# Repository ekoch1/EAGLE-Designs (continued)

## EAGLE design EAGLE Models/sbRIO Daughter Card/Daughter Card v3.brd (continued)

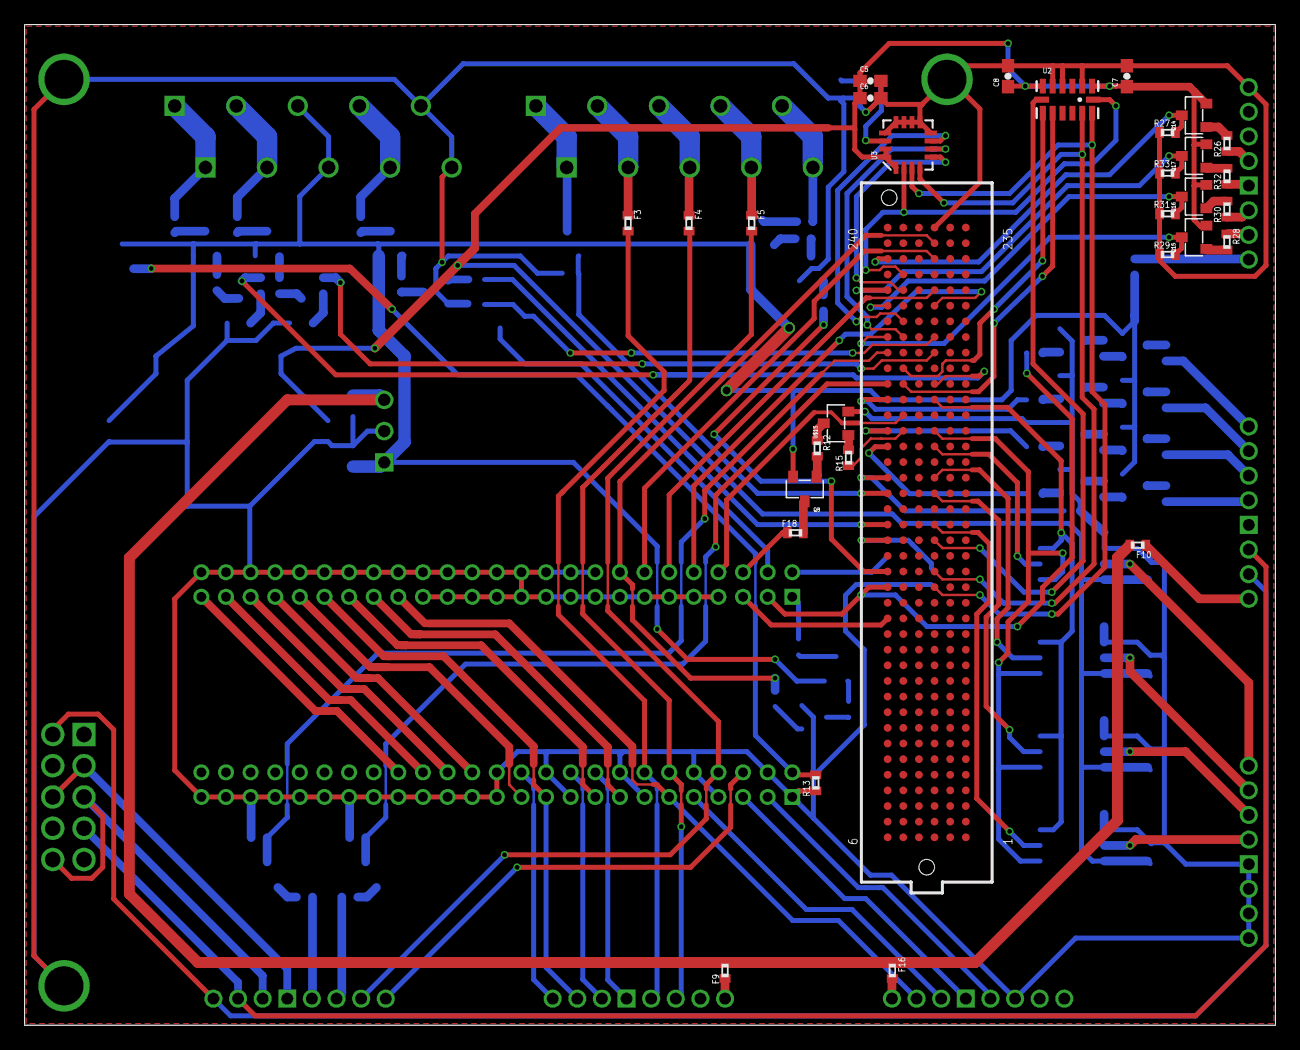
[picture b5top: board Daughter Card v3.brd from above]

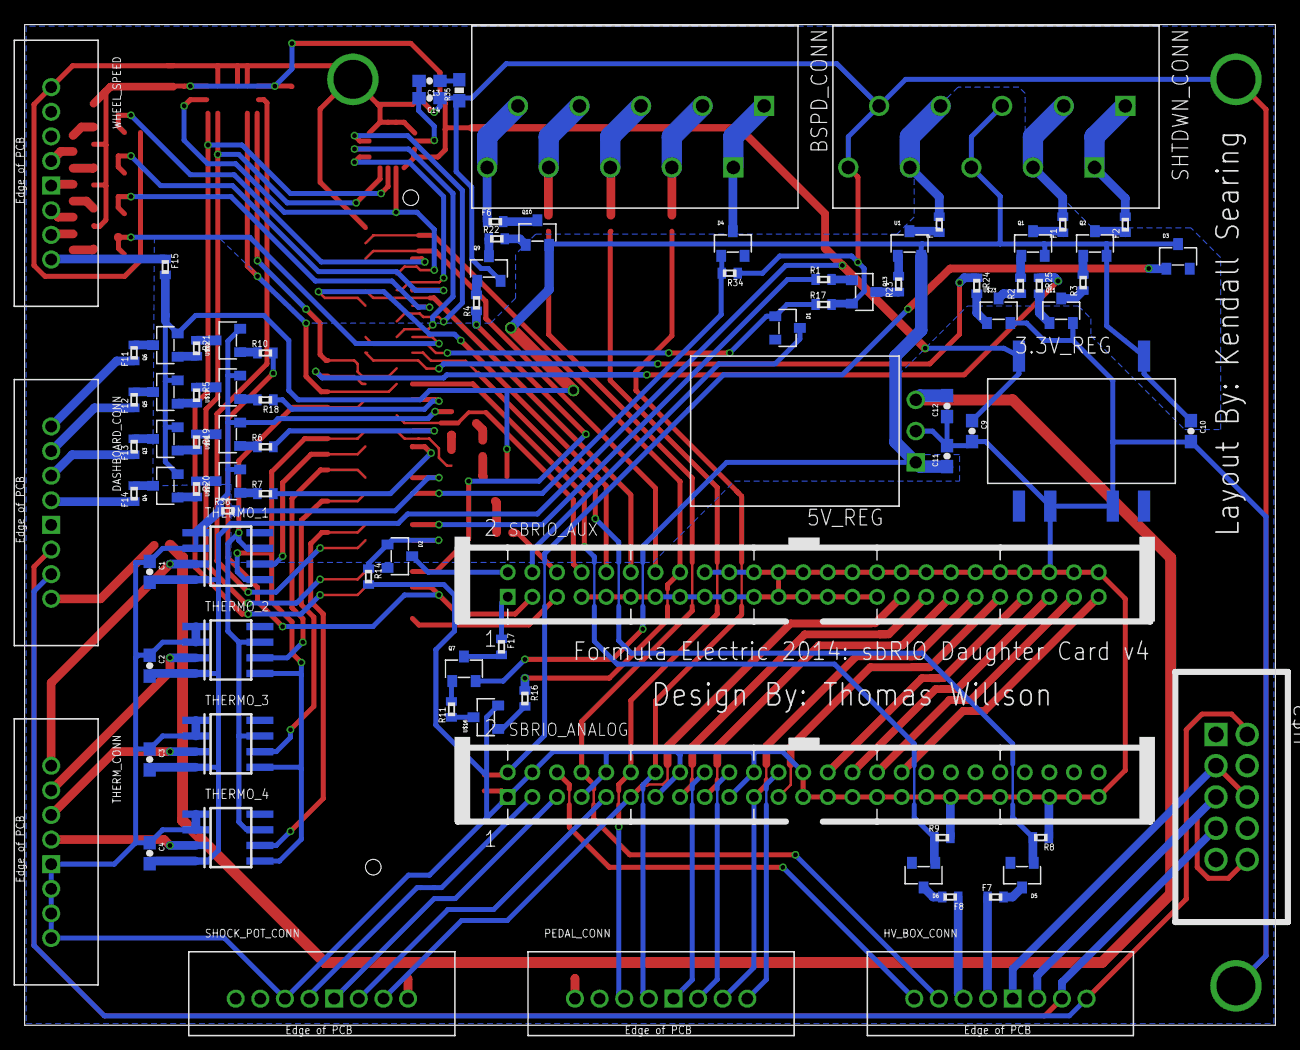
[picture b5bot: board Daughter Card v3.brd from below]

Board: 2 copper layers, 101.6 x 81.3 mm, 119 parts (88 on the bottom side), 146 nets.

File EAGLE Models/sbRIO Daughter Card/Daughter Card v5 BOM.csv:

"Part";"Value";"Device";"Package";"Description";"MF";"MPN";"OC_FARNELL";"OC_NEWARK";
"3.3V_REG";"V7803-1000";"V7803-1000";"V78XX-1000";"";"";"";"";"";
"5V_REG";"V78XX-1500";"V78XX-1500";"V78XX-1500R";"";"";"";"";"";
"ACCUMULATOR_CONN";"RJ45-6L21-S";"RJ45-6L21-S";"RJ45-SHIELD1";"RJ45 Low Profile Shield Type 2";"";"";"unknown";"unknown";
"AIO_PO_CONN";"2516-5";"2516-5";"PAK100/2500-5-16";"3M (TM) Pak 100 4-Wall Header";"";"D2516-5002-AR";"9838376";"12P7055";
"BSPD_CONN";"CONN_5";"CONN_5";"CONNECTOR_5";"";"";"";"";"";
"C5";".1uF";"CAP0603-CAP";"0603-CAP";"Capacitor";"";"";"";"";
"C6";"10uF";"CAP0603-CAP";"0603-CAP";"Capacitor";"";"";"";"";
"C7";".1uF";"CAP0603-CAP";"0603-CAP";"Capacitor";"";"";"";"";
"C8";"1uF";"CAP0603-CAP";"0603-CAP";"Capacitor";"";"";"";"";
"C9";"22uF";"CAP0603-CAP";"0603-CAP";"Capacitor";"";"";"";"";
"C10";"10uF";"CAP0603-CAP";"0603-CAP";"Capacitor";"";"";"";"";
"C11";"10uF";"CAP0603-CAP";"0603-CAP";"Capacitor";"";"";"";"";
"C12";"22uF";"CAP0603-CAP";"0603-CAP";"Capacitor";"";"";"";"";
"C13";"470nF";"CAP0603-CAP";"0603-CAP";"Capacitor";"";"";"";"";
"C14";"10nF";"CAP0603-CAP";"0603-CAP";"Capacitor";"";"";"";"";
"D1";"MMBZ5238B-7-F";"MMBZ5238B-7-F";"SOT-23-3";"Digikey: MMBZ5238B-FDICT-ND";"";"";"";"";
"D2";"MMBZ5238B-7-F";"MMBZ5238B-7-F";"SOT-23-3";"Digikey: MMBZ5238B-FDICT-ND";"";"";"";"";
"D3";"MMBZ5238B-7-F";"MMBZ5238B-7-F";"SOT-23-3";"Digikey: MMBZ5238B-FDICT-ND";"";"";"";"";
"D4";"MMBZ5238B-7-F";"MMBZ5238B-7-F";"SOT-23-3";"Digikey: MMBZ5238B-FDICT-ND";"";"";"";"";
"D5";"MMBZ5238B-7-F";"MMBZ5238B-7-F";"SOT-23-3";"Digikey: MMBZ5238B-FDICT-ND";"";"";"";"";
"D6";"MMBZ5238B-7-F";"MMBZ5238B-7-F";"SOT-23-3";"Digikey: MMBZ5238B-FDICT-ND";"";"";"";"";
"F1";"";"R-EU_R0402";"R0402";"RESISTOR, European symbol";"";"";"";"";
"F2";"";"R-EU_R0402";"R0402";"RESISTOR, European symbol";"";"";"";"";
"F3";"";"R-EU_R0402";"R0402";"RESISTOR, European symbol";"";"";"";"";
"F4";"";"R-EU_R0402";"R0402";"RESISTOR, European symbol";"";"";"";"";
"F5";"";"R-EU_R0402";"R0402";"RESISTOR, European symbol";"";"";"";"";
"F6";"";"R-EU_R0402";"R0402";"RESISTOR, European symbol";"";"";"";"";
"F7";"";"R-EU_R0402";"R0402";"RESISTOR, European symbol";"";"";"";"";
"F8";"";"R-EU_R0402";"R0402";"RESISTOR, European symbol";"";"";"";"";
"F9";"";"R-EU_R0402";"R0402";"RESISTOR, European symbol";"";"";"";"";
"F10";"";"R-EU_R0402";"R0402";"RESISTOR, European symbol";"";"";"";"";
"F14";"";"R-EU_R0402";"R0402";"RESISTOR, European symbol";"";"";"";"";
"F15";"";"R-EU_R0402";"R0402";"RESISTOR, European symbol";"";"";"";"";
"F16";"";"R-EU_R0402";"R0402";"RESISTOR, European symbol";"";"";"";"";
"F17";"";"R-EU_R0402";"R0402";"RESISTOR, European symbol";"";"";"";"";
"F18";"";"R-EU_R0402";"R0402";"RESISTOR, European symbol";"";"";"";"";
"F19";"";"R-EU_R0402";"R0402";"RESISTOR, European symbol";"";"";"";"";
"F20";"";"R-EU_R0402";"R0402";"RESISTOR, European symbol";"";"";"";"";
"F21";"";"R-EU_R0402";"R0402";"RESISTOR, European symbol";"";"";"";"";
"F22";"";"R-EU_R0402";"R0402";"RESISTOR, European symbol";"";"";"";"";
"IC1";"BTS716G";"BTS716G";"PG-DSO-20";"Smart High-Side Power Switch Four Channels: 4 x 140mOhm staus Feedback";"";"";"unknown";"unknown";
"IC2";"BTS716G";"BTS716G";"PG-DSO-20";"Smart High-Side Power Switch Four Channels: 4 x 140mOhm staus Feedback";"";"";"unknown";"unknown";
"IC3";"BTS716G";"BTS716G";"PG-DSO-20";"Smart High-Side Power Switch Four Channels: 4 x 140mOhm staus Feedback";"";"";"unknown";"unknown";
"Q7";"MMBT4403-7-F";"MMBT4403-7-F";"SOT-23-3";"";"";"";"";"";
"Q8";"MMBT4403-7-F";"MMBT4403-7-F";"SOT-23-3";"";"";"";"";"";
"R8";"10k";"R-US_R0402";"R0402";"RESISTOR, American symbol";"";"";"";"";
"R9";"10k";"R-US_R0402";"R0402";"RESISTOR, American symbol";"";"";"";"";
"R11";"4.7k";"R-US_R0402";"R0402";"RESISTOR, American symbol";"";"";"";"";
"R12";"4.7k";"R-US_R0402";"R0402";"RESISTOR, American symbol";"";"";"";"";
"R13";"10k";"R-US_R0402";"R0402";"RESISTOR, American symbol";"";"";"";"";
"R14";"10k";"R-US_R0402";"R0402";"RESISTOR, American symbol";"";"";"";"";
"R15";"4.7k";"R-US_R0402";"R0402";"RESISTOR, American symbol";"";"";"";"";
"R16";"4.7k";"R-US_R0402";"R0402";"RESISTOR, American symbol";"";"";"";"";
"R17";"10k";"R-US_R0402";"R0402";"RESISTOR, American symbol";"";"";"";"";
"R34";"10k";"R-US_R0402";"R0402";"RESISTOR, American symbol";"";"";"";"";
"R35";"10K";"RESISTOR0603-RES";"0603-RES";"Resistor";"";"";"";"";
"R36";"10k";"R-US_R0402";"R0402";"RESISTOR, American symbol";"";"";"";"";
"SBRIO_ANALOG";"SBRIO_MIO";"SBRIO_MIO";"SBRIO_J502_J503";"";"";"";"";"";
"SBRIO_AUX";"SBRIO_AUX";"SBRIO_AUX";"SBRIO_J502_J503";"An output for a lot of the extra pins on the sbRIO.";"";"";"";"";
"SHTDWN_CONN";"CONN_5";"CONN_5";"CONNECTOR_5";"";"";"";"";"";
"TUB_CONN";"2516-5";"2516-5";"PAK100/2500-5-16";"3M (TM) Pak 100 4-Wall Header";"";"D2516-5002-AR";"9838376";"12P7055";
"U$2";"SBRIO_W500";"SBRIO_W500";"SBRIO_W";"";"";"";"";"";
"U$3";"SBRIO_RMC";"SBRIO_RMC";"SEAM-40-XX.X-XX-06-X-A";"";"";"";"";"";
"U$15";"MMBT4401-7-F";"MMBT4401-7-F";"SOT-23-3";"";"";"";"";"";
"U$16";"MMBT4401-7-F";"MMBT4401-7-F";"SOT-23-3";"";"";"";"";"";
"U1";"";"TXB0104PWR";"TSSOP14";"4-Bit Bi-Directional Level Shifter";"";"";"";"";
"U2";"ADXL345";"ADXL345";"LGA14";"3-axis SPI/I2C 2/4/8/16g accelerometer";"";"";"";"";
"U3";"L3G4200D";"L3G4200D";"LGA16-4X4";"L3G4200D Three-axis, digital output gyroscope";"";"";"";"";
"X1";"5566-2";"5566-2";"5566-2";"Mini FIT connector 2 pol";"";"";"1822072";"unknown";
"X2";"";"FTOP-4";"FTOP-4";"AMP connector";"";"";"";"";
